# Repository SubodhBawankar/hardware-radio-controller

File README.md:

# hardware-radio-controller
PCB design for Radio Controller using ESP32 and NRF24L01 module.
This is my practice project. Feel free to point mistakes.

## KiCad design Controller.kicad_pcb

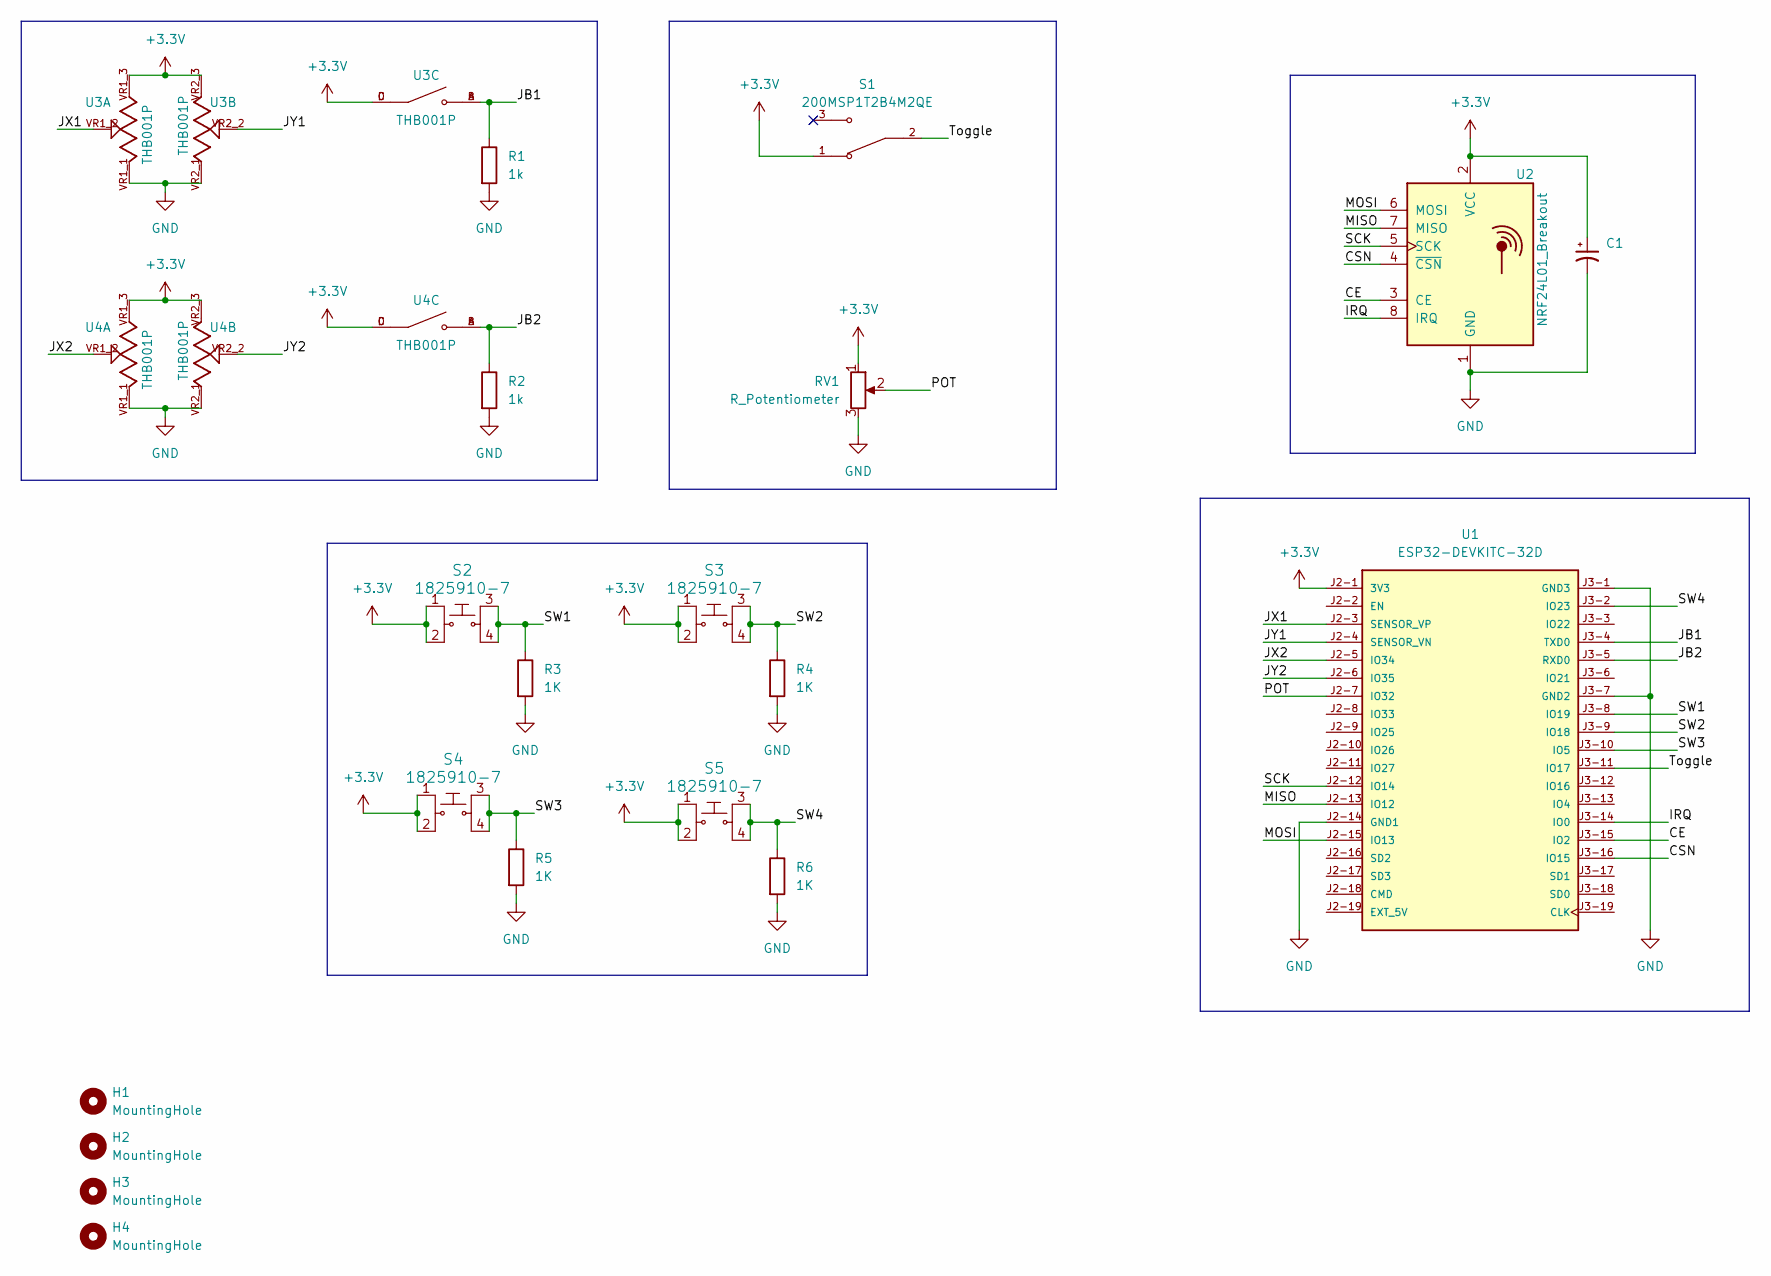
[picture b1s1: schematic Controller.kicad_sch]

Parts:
C1: C_Polarized_Small_US; CP_Radial_D5.0mm_P2.50mm
H1, H2, H3, H4: MountingHole; MountingHole_2.1mm
R1, R2: 1k; R_Axial_DIN0204_L3.6mm_D1.6mm_P5.08mm_Horizontal
R3, R4, R5, R6: 1K; R_Axial_DIN0204_L3.6mm_D1.6mm_P5.08mm_Horizontal
RV1: R_Potentiometer; Potentiometer_Alps_RK09K_Single_Vertical
S1: 200MSP1T2B4M2QE; SW_200MSP1T2B4M2QE; PARTREV A
S2, S3, S4, S5: 1825910-7; Switch_Tactile_THT_6x6mm; MPN 1825910-7; Digi-Key_PN 450-1804-ND
U1: ESP32-DEVKITC-32D; MODULE_ESP32-DEVKITC-32D
U2: NRF24L01_Breakout; nRF24L01_Breakout
U3, U4: THB001P; CNK_THB001P

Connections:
+3.3V: C1.1, RV1.1, S1.1, S2.1, S2.2, S3.1, S3.2, S4.1, S4.2, S5.1, S5.2, U1.J2-1 (3V3), U2.2 (VCC), U3.C, U3.D, U3.VR1_3, U3.VR2_3, U4.C, U4.D, U4.VR1_3, U4.VR2_3
/CE: U1.J3-15 (IO2), U2.3 (CE)
/CSN: U1.J3-16 (IO15), U2.4 (~CSN)
/IRQ: U1.J3-14 (IO0), U2.8 (IRQ)
/JB1: R1.1, U1.J3-4 (TXD0), U3.A, U3.B
/JB2: R2.1, U1.J3-5 (RXD0), U4.A, U4.B
/JX1: U1.J2-3 (SENSOR_VP), U3.VR1_2
/JX2: U1.J2-5 (IO34), U4.VR1_2
/JY1: U1.J2-4 (SENSOR_VN), U3.VR2_2
/JY2: U1.J2-6 (IO35), U4.VR2_2
/MISO: U1.J2-13 (IO12), U2.7 (MISO)
/MOSI: U1.J2-15 (IO13), U2.6 (MOSI)
/POT: RV1.2, U1.J2-7 (IO32)
/SCK: U1.J2-12 (IO14), U2.5 (SCK)
/SW1: R3.1, S2.3, S2.4, U1.J3-8 (IO19)
/SW2: R4.1, S3.3, S3.4, U1.J3-9 (IO18)
/SW3: R5.1, S4.3, S4.4, U1.J3-10 (IO5)
/SW4: R6.1, S5.3, S5.4, U1.J3-2 (IO23)
/Toggle: S1.2, U1.J3-11 (IO17)
GND: C1.2, R1.2, R2.2, R3.2, R4.2, R5.2, R6.2, RV1.3, U1.J2-14 (GND1), U1.J3-1 (GND3), U1.J3-7 (GND2), U2.1 (GND), U3.VR1_1, U3.VR2_1, U4.VR1_1, U4.VR2_1

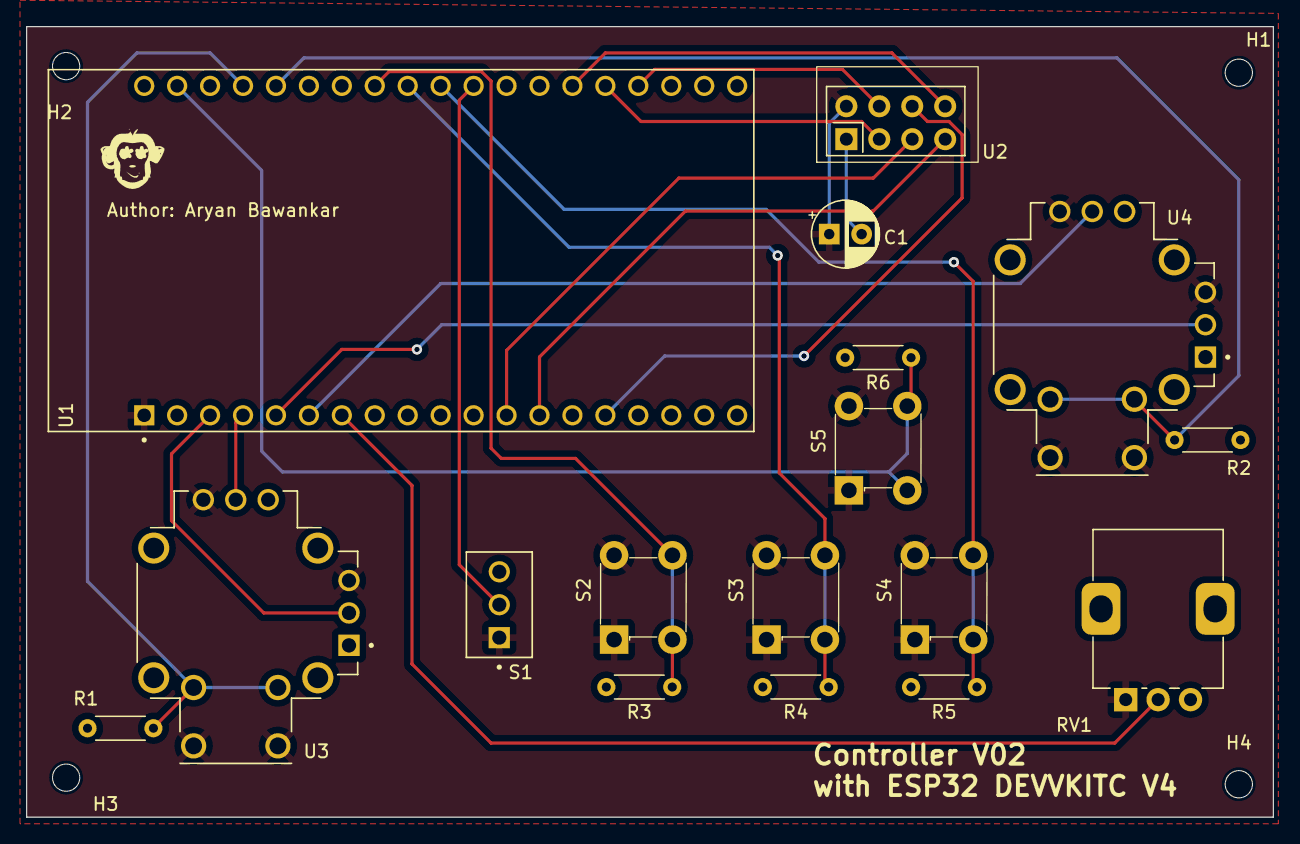
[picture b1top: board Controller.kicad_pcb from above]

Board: 2 copper layers, 96.1 x 61.0 mm, 21 parts (0 on the bottom side), 20 nets.

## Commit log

2023-06-29 Uploading project on Github
